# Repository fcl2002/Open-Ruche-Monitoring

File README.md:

# Open Ruche 🐝 — BEE SMART

**Système de Monitorage Autonome de Ruches en Temps-réel**  
_Protéger les abeilles, préserver demain._

An intelligent beehive monitoring solution combining embedded AI, LoRaWAN communication, and solar power to help beekeepers protect their colonies and optimize hive management.

---

## Context & Motivation

Bee colonies face an accelerating global decline driven by the *Varroa destructor* mite, the Asian hornet (*Vespa velutina*), pesticides, and climate change. Continuous 24/7 manual monitoring is impossible for beekeepers — Open Ruche fills that gap with autonomous, real-time surveillance and automatic threat detection.

---

## Team

| Role | Name |
|------|------|
| **Project Manager, System Integration & Firmware Lead** | [Fernando COSTA LASMAR](https://www.linkedin.com/in/fernando-costa-lasmar/) |
| **AI/ML Engineer & Model Development** | [Flávio ROSIM DE SOUSA](https://www.linkedin.com/in/flávio-rosim-de-sousa/) |
| **Hardware Design & PCB Engineer** | [Matheus SISTON GALDINO](https://www.linkedin.com/in/matheussistongaldino/) |
| **Power Management & Solar Systems** | [Karim SAWAYA](https://www.linkedin.com/in/karim-sawaya-67ab87292/) |
| **HMI & Documentation** | [Yan DING](mailto:dingyan02040608@gmail.com) |

**Academic context:** Polytech Sorbonne — EI4 FISE | Projet Systèmes Embarqués IoT 2025-2026 | Groupe 4 – Ruche 9

---

## Solution Overview

Open Ruche is built around four integrated layers:

**Power Layer**
- Solar panel + battery with charge management module
- Switchable voltage regulator for load optimization
- Deep Sleep mode bringing average draw down to ~0.822 mA

**Sensor Layer (custom PCB)**
- Temperature: 2× DS18B20 probes (internal) + 1× DHT22 (external T°/humidity)
- Weight: HX711 load cell amplifier
- Light: LUX sensor
- Motion/safety: MMA8452 accelerometer, GPS module, buzzer alarm
- Air quality: gas/particle sensor (SEN0190)

**AI Processing Layer**
- Dual-core setup: Arduino Nano 3.3 (audio) + XIAO ESP32S3 (vision)
- TensorFlow Lite models running fully on-device
- **Audio classification model** — 86.45% accuracy on test data
  - Class 1: Normal activity
  - Class 2: Swarming
  - Class 3: Queenless colony
- **Hornet detection model (computer vision)** — 79.7% accuracy, F1-score 90%
  - Code 0: No hornet detected
  - Code 1: Hornet detected

**Communication & Cloud Layer**
- LoRaWAN module → The Things Network (TTN)
- Configurable uplink frequency via TTN downlink
- Cloud dashboards: BEEP Monitor + Datacake
- Real-time alerts and remote parameter configuration

---

## Software Architecture

The firmware implements a 4-state machine to minimise power consumption:

```
BOOT → INIT → LECTURE (sensors + AI) → DEEP SLEEP
              ↑___________________________________|
              Wake after configurable interval
```

- **INIT → LECTURE** triggered when LUX > 100 AND internal temp > 20 °C  
- **LECTURE → DEEP SLEEP** when LUX < 100 OR internal temp < 15 °C  
- LoRa downlink allows remote configuration of the sleep interval  
- Logging system for debugging and field maintenance

---

## Power Consumption

| Phase | Average Current |
|-------|----------------|
| Active period (AI + sensors + LoRa) | ~85.8 mA |
| Deep Sleep | ~0.822 mA |

Charge breakdown per cycle (54 s total):
- AI (10 s): 0.414 mAh — 38%
- Sensors (15 s): 0.283 mAh — 26%
- LoRa (9 s): 0.117 mAh — 11%
- Deep Sleep (20 min): 0.274 mAh — 25%

**Estimated autonomy (1000 mAh battery):** ~13 days without solar charging.

---

## Project Status

| Objective | Status |
|-----------|--------|
| Sensor accuracy & LoRa transmission | ✅ Done |
| Real-time image & audio AI detection | ✅ Done |
| Alarm creation & notifications | ✅ Done |
| Remote parameter & alarm configuration | ✅ Done |
| System energy autonomy | ✅ Done |
| PCB schematic & assembly | ✅ Done |
| Enclosure fabrication & prototype wiring | ✅ Done |
| Data display on cloud platforms | ✅ Done |
| Accelerometer for fall/theft detection | ❌ Not implemented |

---

## Getting Started

### Prerequisites

- Arduino IDE or PlatformIO
- KiCad (for hardware design)
- The Things Network account + LoRaWAN gateway access

### Quick Start

```bash
# Clone the repository
git clone https://github.com/[your-username]/OpenRuche.git
cd OpenRuche

# Project structure
# hardware/   — KiCad schematics & PCB files
# software/   — Firmware (Arduino / PlatformIO)
# ai/         — TensorFlow Lite model training scripts
# docs/       — Documentation & guides
```

For detailed development guidelines, see [CONTRIBUTING.md](CONTRIBUTING.md).

---

## License

This project is open-source. See [LICENSE](LICENSE) for details.

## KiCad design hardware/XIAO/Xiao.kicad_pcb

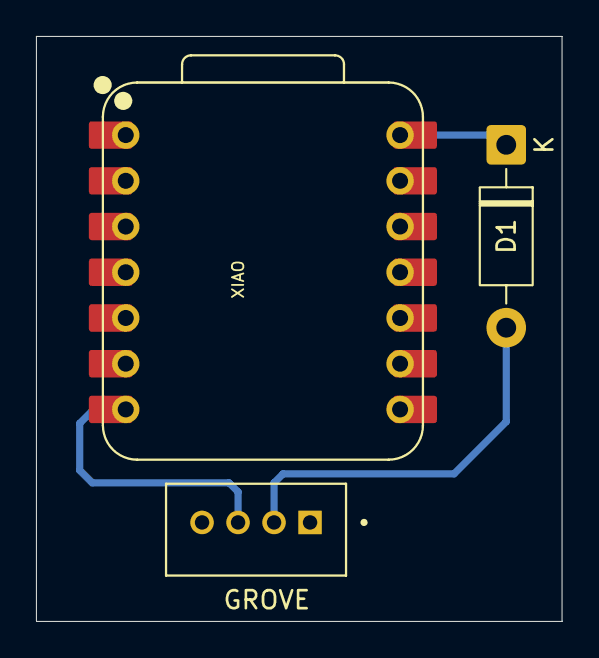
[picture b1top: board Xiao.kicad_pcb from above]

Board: 2 copper layers, 29.2 x 32.5 mm, 3 parts (0 on the bottom side), 4 nets.

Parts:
D1: 1N5817; D_DO-41_SOD81_P10.16mm_Horizontal
J1: GROVE; SEEED_110990030
XIAO: XIAO-ESP32-S3-DIP

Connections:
/+5V: D1.2 (A), J1.2 (VCC)
/TX_XIAO: J1.3 (SIG1), XIAO.7 (GPIO43_D6_TX)
GND: J1.1 (GND), XIAO.13 (GND)
unnamed: D1.1 (K), XIAO.14 (VBUS)

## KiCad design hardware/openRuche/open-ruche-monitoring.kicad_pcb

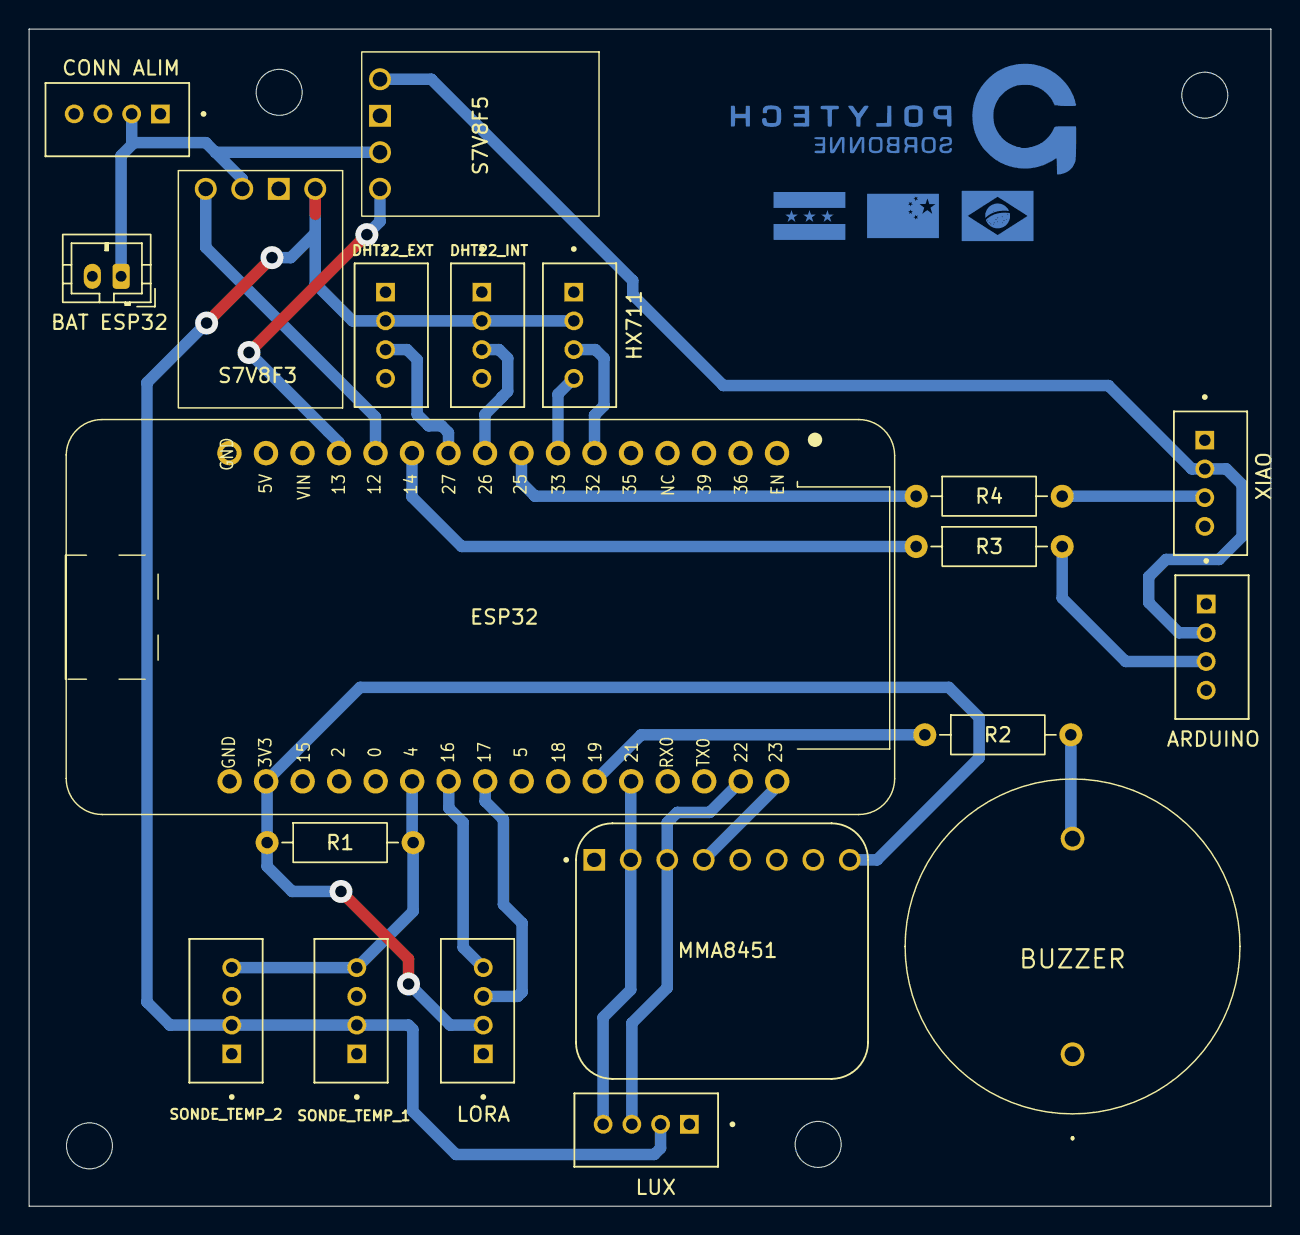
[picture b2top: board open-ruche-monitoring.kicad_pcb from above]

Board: 2 copper layers, 86.4 x 81.9 mm, 20 parts (0 on the bottom side), 23 nets.

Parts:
BUZZER: KPEG222
J1: HX711; SEEED_110990030
J2: DHT22_EXT; SEEED_110990030
J3: DHT22_INT; SEEED_110990030
J4: SONDE_TEMP_1; SEEED_110990030
J5: SONDE_TEMP_2; SEEED_110990030
J6: LUX; SEEED_110990030
J7: LORA; SEEED_110990030
J8: ARDUINO; SEEED_110990030
J9: XIAO; SEEED_110990030
J10: MMA8451; MODULE_2019
J11: CONN ALIM; SEEED_110990030
J12: BAT ESP32; JST_PH_B2B-PH-K_1x02_P2.00mm_Vertical
R1: 4.7k; R_Axial_DIN0207_L6.3mm_D2.5mm_P10.16mm_Horizontal
R2: 100; R_Axial_DIN0207_L6.3mm_D2.5mm_P10.16mm_Horizontal
R3, R4: 1k; R_Axial_DIN0207_L6.3mm_D2.5mm_P10.16mm_Horizontal
U1: uPesy ESP32 Wroom Low Power DevKit; uPesy_ESP32_Wroom_Low_Power_DevKit
U2: S7V8F3; MODULE_STEP-DOWN_VOLTAGE_REGULATOR_D24V6F3
U3: S7V8F5; MODULE_STEP-DOWN_VOLTAGE_REGULATOR_D24V6F3

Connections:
/+3.3V: J7.2 (VCC), J10.8, R1.1, U1.31 (3V3)
/+3.3V_REG: J1.2 (VCC), J2.2 (VCC), J3.2 (VCC), J4.2 (VCC), J5.2 (VCC), J6.2 (VCC), U2.VOUT
/+3.7V: J11.2 (VCC), J12.1, U2.VIN, U3.VIN
/+5V_REG: J8.2 (VCC), J9.2 (VCC), U3.VOUT
/BUZZER: R2.1, U1.22 (GPIO19)
/DATA_DHT22_EXT: J2.3 (SIG1), U1.10 (GPIO27)
/DATA_DHT22_INT: J3.3 (SIG1), U1.9 (GPIO26)
/DOUT: J1.3 (SIG1), U1.6 (GPIO32)
/EN_3.3V_REG: U1.12 (GPIO12), U2.!SHDN (~SHDN)
/EN_5V_REG: U1.13 (GPIO13), U3.!SHDN (~SHDN)
/I1: J10.4, U1.17 (GPIO23)
/ONE_WIRE_TEMP: J4.4 (SIG2), J5.4 (SIG2), R1.2, U1.27 (GPIO4)
/PSCK: J1.4 (SIG2), U1.7 (GPIO33)
/RX_LORA: J7.3 (SIG1), U1.25 (GPIO17)
/SCL: J6.3 (SIG1), J10.3, U1.18 (GPIO22)
/SDA: J6.4 (SIG2), J10.2, U1.21 (GPIO21)
/TX_ARDUINO: R3.1, U1.11 (GPIO14)
/TX_LORA: J7.4 (SIG2), U1.26 (GPIO16)
/TX_XIAO: R4.1, U1.8 (GPIO25)
GND: BUZZER.1 (-), J1.1 (GND), J2.1 (GND), J3.1 (GND), J4.1 (GND), J5.1 (GND), J6.1 (GND), J7.1 (GND), J8.1 (GND), J9.1 (GND), J10.7, J11.1 (GND), J12.2, U1.16 (GND), U1.23 (GPIO18), U1.32 (GND), U2.GND, U3.GND
unnamed: J8.3 (SIG1), R3.2
unnamed: J9.3 (SIG1), R4.2
unnamed: BUZZER.2 (+), R2.2

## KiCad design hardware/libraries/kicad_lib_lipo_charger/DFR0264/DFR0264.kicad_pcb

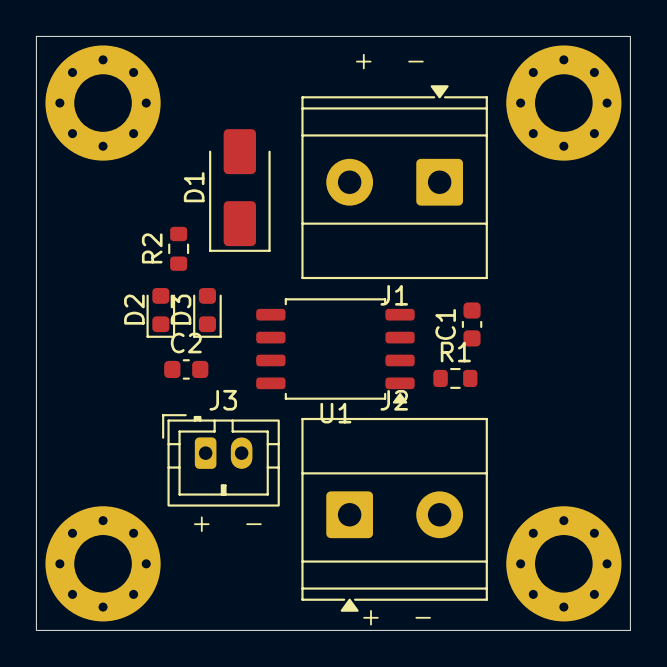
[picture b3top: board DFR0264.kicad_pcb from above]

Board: 2 copper layers, 33.0 x 33.0 mm, 11 parts (0 on the bottom side), 8 nets, no tracks yet.

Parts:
C1, C2: C; C_0603_1608Metric
D1: SS14; D_SMA
D2, D3: LED; LED_0603_1608Metric
J1, J2: Conn_01x02; TerminalBlock_Phoenix_MKDS-1,5-2_1x02_P5.00mm_Horizontal
J3: Conn_01x02; JST_PH_B2B-PH-K_1x02_P2.00mm_Vertical
R1, R2: R; R_0603_1608Metric
U1: CN3063; SOIC-8_5.3x5.3mm_P1.27mm

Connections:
GND: C1.2, C2.2, J1.1, J2.2, J3.2, R2.2, U1.1 (TEMP), U1.3 (GND)
unnamed: D1.2 (A), J1.2
unnamed: C1.1, D1.1 (K), R1.1, U1.4 (VIN)
unnamed: D2.2 (A), D3.2 (A), R1.2
unnamed: D2.1 (K), U1.6 (~DONE)
unnamed: D3.1 (K), U1.7 (~CHRG)
unnamed: C2.1, J2.1, J3.1, U1.5 (BAT), U1.8 (FB)
unnamed: R2.1, U1.2 (ISET)

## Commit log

2026-02-09 chore(init): configure project structure and development rules
2026-02-10 chore(init): add .gitignore file
2026-02-10 chore(init): gitignore update
2026-02-17 hw(schematic): initialize KiCad project and create main schematic file
2026-02-23 feat(hx711): finish HX711 load cell calibration and configuration
2026-02-23 refactor: move load cell logic to function
2026-02-23 hw(schematic): add sensors to schematic
2026-02-24 refactor: move global sensor definitions to sensors.h and sensors.c files
2026-02-24 feat(sondes): add DS18B20 temperature probes
2026-02-24 feat(light sensor): payload structure + light sensor configured
2026-02-24 feat: add logger system and improve error handling
2026-02-24 feat: read accelerometer MMA 8 451 to the project
2026-02-24 hw(schematic): add acc and 3.3V conversor schematic
2026-02-24 hw(schematic): changes to 3.3V conversor footprint
2026-03-02 fix(sensors): set fixed offset for HX711 tare value
2026-03-02 feat(payload): integrate HX711 load cell reading into transmission payload
2026-03-02 hw(schematic): schematic done
2026-03-09 hw(3D) Add 3D models for lora, hx711 and lipo charger
2026-03-09 hw(pcb) save pcb to try another layout
2026-03-09 refactor: modularize project structure and improve sensor initialization logging
2026-03-10 hw(pcb) pcb done
2026-03-10 hw(pcb) main pcb changes
2026-03-10 hw(pcb) pcb xiao
2026-03-10 hw(pcb) gerber files
2026-03-11 feat(lora): add TTN LoRa-E5 module integration with payload pipeline and test mode
2026-03-24 hw(pcb) final commit pcb
2026-03-31 soutenance 3
2026-03-31 soutence 3: implementation finale sans souder
2026-04-01 refactor files to /include
2026-04-02 module LoRa configured
2026-04-02 LoRa config with deep sleep mode enable and wake up
2026-04-02 refactor boards function names + LoRa config to receive downlink
2026-04-02 LoRa downlink configured to DEEP_SLEEP_DURATION_S (freq d'envoi)
2026-04-08 deep sleep interval update and wake up conditions set
2026-04-10 bug fix: LoRa wakeup
2026-04-10 bug fix: dormant mode
2026-04-10 change: DEEP_SLEEP_LORA_S
2026-04-13 fix: lux sleep consummation
2026-05-01 fix: file organization
